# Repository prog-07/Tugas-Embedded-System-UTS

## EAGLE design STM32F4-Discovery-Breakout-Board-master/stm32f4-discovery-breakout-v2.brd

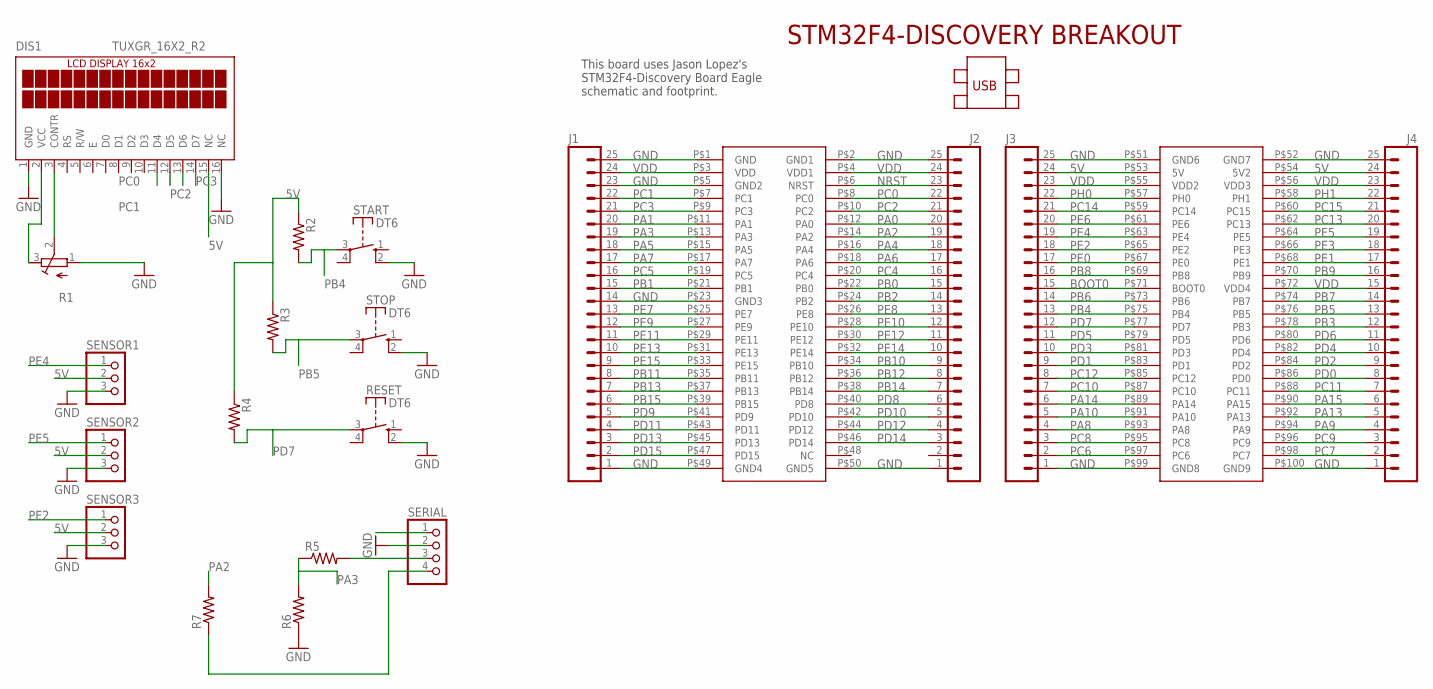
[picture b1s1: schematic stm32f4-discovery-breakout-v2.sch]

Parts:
DIS1: TUXGR_16X2_R2
J1, J2, J3, J4: M25LOCK_LONGPADS; 1X25_LOCK_LONGPADS
R1: R-TRIMM3339P; RTRIM3339P
R2, R3, R4, R5, R6, R7: R-US_0207/10; 0207/10
RESET: DT6
SENSOR1, SENSOR2, SENSOR3: PINHD-1X3; 1X03
SERIAL: PINHD-1X4; 1X04
START: DT6
STOP: DT6
U$1: STM32F4-DISCOVERY

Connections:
BOOT0: J3.15, U$1.P$71 (BOOT0)
unnamed: DIS1.2 (VCC), R1.3 (A)
unnamed: DIS1.3 (CONTR), R1.2 (S)
unnamed: R5.2, SERIAL.3
unnamed: R7.1, SERIAL.4
NRST: J2.23, U$1.P$6 (NRST)
PA0: J2.20, U$1.P$12 (PA0)
PA1: J1.20, U$1.P$11 (PA1)
PA2: J2.19, R7.2, U$1.P$14 (PA2)
PA3: J1.19, R5.1, R6.2, U$1.P$13 (PA3)
PA4: J2.18, U$1.P$16 (PA4)
PA5: J1.18, U$1.P$15 (PA5)
PA6: J2.17, U$1.P$18 (PA6)
PA7: J1.17, U$1.P$17 (PA7)
PA8: J3.4, U$1.P$93 (PA8)
PA9: J4.4, U$1.P$94 (PA9)
PA10: J3.5, U$1.P$91 (PA10)
PA13: J4.5, U$1.P$92 (PA13)
PA14: J3.6, U$1.P$89 (PA14)
PA15: J4.6, U$1.P$90 (PA15)
PB0: J2.15, U$1.P$22 (PB0)
PB1: J1.15, U$1.P$21 (PB1)
PB2: J2.14, U$1.P$24 (PB2)
PB3: J4.12, U$1.P$78 (PB3)
PB4: J3.13, R2.2, START.3, U$1.P$75 (PB4)
PB5: J4.13, R3.2, STOP.3, U$1.P$76 (PB5)
PB6: J3.14, U$1.P$73 (PB6)
PB7: J4.14, U$1.P$74 (PB7)
PB8: J3.16, U$1.P$69 (PB8)
PB9: J4.16, U$1.P$70 (PB9)
PB10: J2.9, U$1.P$34 (PB10)
PB11: J1.8, U$1.P$35 (PB11)
PB12: J2.8, U$1.P$36 (PB12)
PB13: J1.7, U$1.P$37 (PB13)
PB14: J2.7, U$1.P$38 (PB14)
PB15: J1.6, U$1.P$39 (PB15)
PC0: DIS1.11 (D4), J2.22, U$1.P$8 (PC0)
PC1: DIS1.12 (D5), J1.22, U$1.P$7 (PC1)
PC2: DIS1.13 (D6), J2.21, U$1.P$10 (PC2)
PC3: DIS1.14 (D7), J1.21, U$1.P$9 (PC3)
PC4: J2.16, U$1.P$20 (PC4)
PC5: J1.16, U$1.P$19 (PC5)
PC6: J3.2, U$1.P$97 (PC6)
PC7: J4.2, U$1.P$98 (PC7)
PC8: J3.3, U$1.P$95 (PC8)
PC9: J4.3, U$1.P$96 (PC9)
PC10: J3.7, U$1.P$87 (PC10)
PC11: J4.7, U$1.P$88 (PC11)
PC12: J3.8, U$1.P$85 (PC12)
PC13: J4.20, U$1.P$62 (PC13)
PC14: J3.21, U$1.P$59 (PC14)
PC15: J4.21, U$1.P$60 (PC15)
PD0: J4.8, U$1.P$86 (PD0)
PD1: J3.9, U$1.P$83 (PD1)
PD2: J4.9, U$1.P$84 (PD2)
PD3: J3.10, U$1.P$81 (PD3)
PD4: J4.10, U$1.P$82 (PD4)
PD5: J3.11, U$1.P$79 (PD5)
PD6: J4.11, U$1.P$80 (PD6)
PD7: J3.12, R4.2, RESET.3, U$1.P$77 (PD7)
PD8: J2.6, U$1.P$40 (PD8)
PD9: J1.5, U$1.P$41 (PD9)
PD10: J2.5, U$1.P$42 (PD10)
PD11: J1.4, U$1.P$43 (PD11)
PD12: J2.4, U$1.P$44 (PD12)
PD13: J1.3, U$1.P$45 (PD13)
PD14: J2.3, U$1.P$46 (PD14)
PD15: J1.2, U$1.P$47 (PD15)
PE0: J3.17, U$1.P$67 (PE0)
PE1: J4.17, U$1.P$68 (PE1)
PE2: J3.18, SENSOR3.1, U$1.P$65 (PE2)
PE3: J4.18, U$1.P$66 (PE3)
PE4: J3.19, SENSOR1.1, U$1.P$63 (PE4)
PE5: J4.19, SENSOR2.1, U$1.P$64 (PE5)
PE6: J3.20, U$1.P$61 (PE6)
PE7: J1.13, U$1.P$25 (PE7)
PE8: J2.13, U$1.P$26 (PE8)
PE9: J1.12, U$1.P$27 (PE9)
PE10: J2.12, U$1.P$28 (PE10)
PE11: J1.11, U$1.P$29 (PE11)
PE12: J2.11, U$1.P$30 (PE12)
PE13: J1.10, U$1.P$31 (PE13)
PE14: J2.10, U$1.P$32 (PE14)
PE15: J1.9, U$1.P$33 (PE15)
PH0: J3.22, U$1.P$57 (PH0)
PH1: J4.22, U$1.P$58 (PH1)
VDD: J1.24, J2.24, J3.23, J4.15, J4.23, U$1.P$3 (VDD), U$1.P$4 (VDD1), U$1.P$55 (VDD2), U$1.P$56 (VDD3), U$1.P$72 (VDD4)

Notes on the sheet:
This board uses Jason Lopez's STM32F4-Discovery Board Eagle schematic and footprint.

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
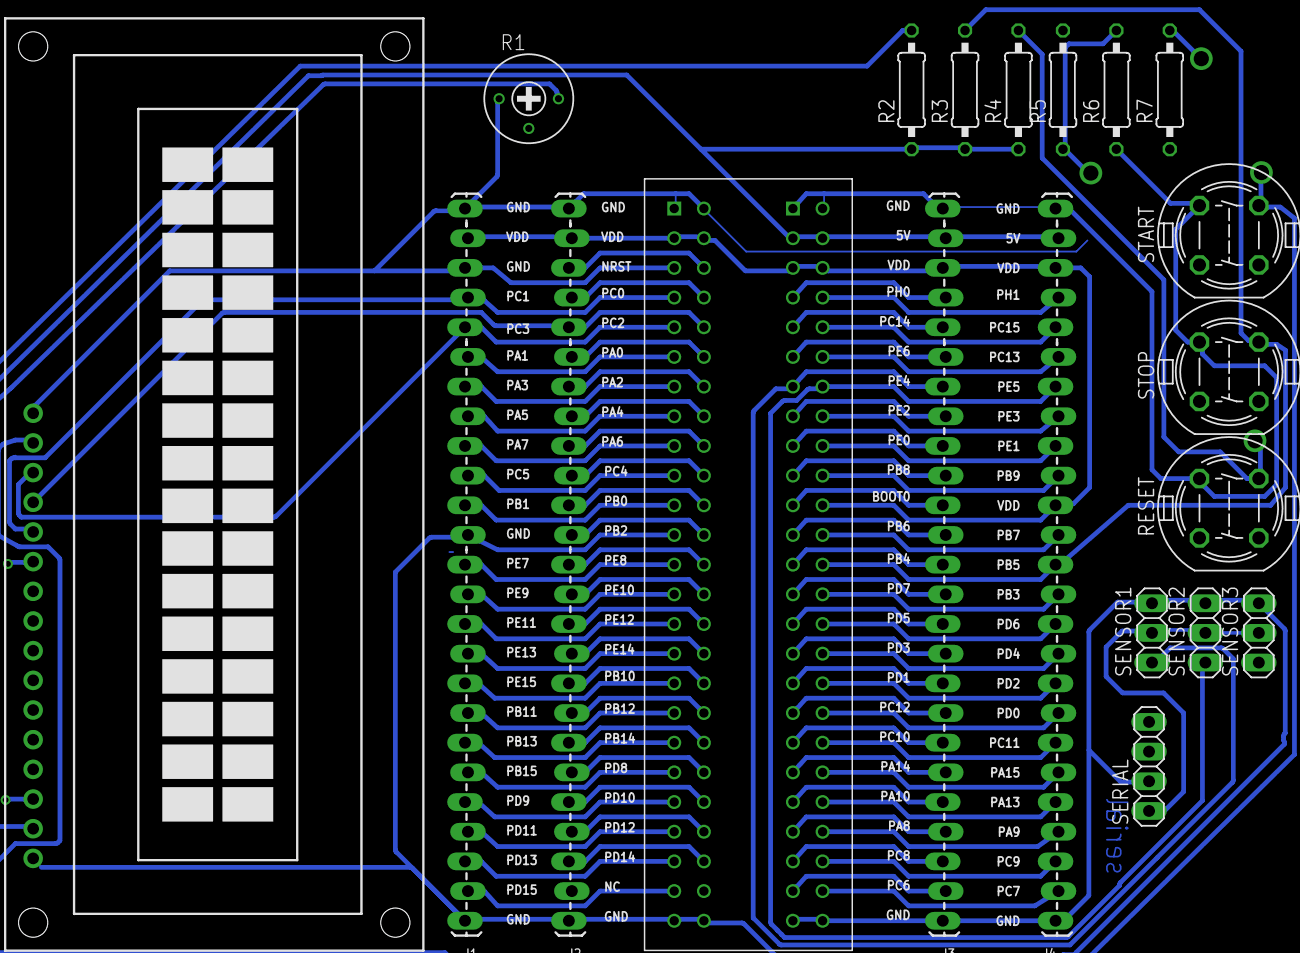
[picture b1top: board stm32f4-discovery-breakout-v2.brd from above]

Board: 2 copper layers, 20 parts (0 on the bottom side), 89 nets.

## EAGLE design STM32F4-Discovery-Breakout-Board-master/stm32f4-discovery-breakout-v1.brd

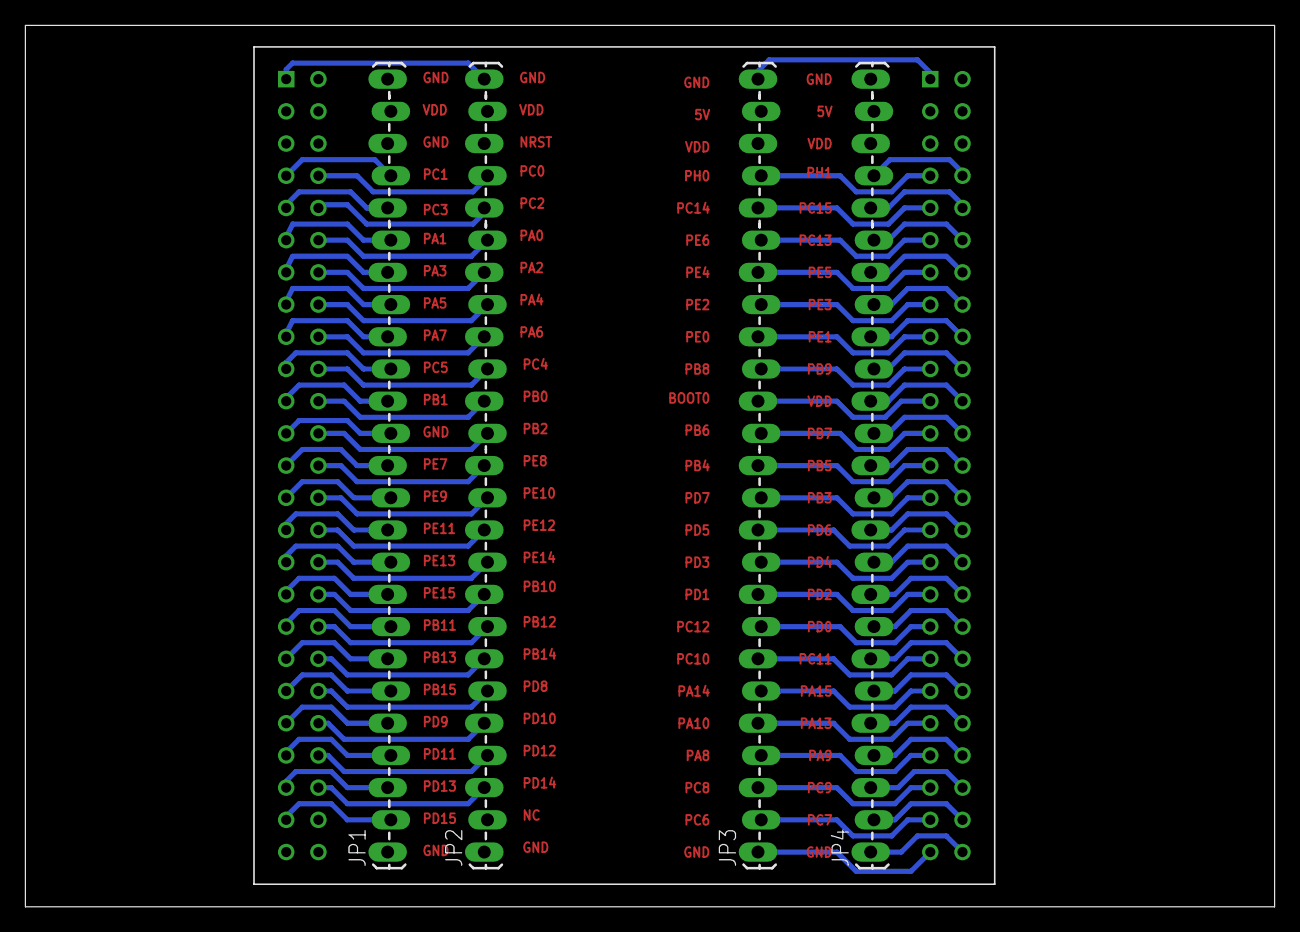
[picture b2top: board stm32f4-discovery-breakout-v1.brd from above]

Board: 2 copper layers, 98.5 x 69.5 mm, 5 parts (0 on the bottom side), 85 nets.

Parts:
JP1, JP2, JP3, JP4: M25LOCK_LONGPADS; 1X25_LOCK_LONGPADS
U$1: STM32F4-DISCOVERY

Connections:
5V: JP3.24, JP4.24, U$1.P$53, U$1.P$54
BOOT0: JP3.15, U$1.P$71
GND: JP1.1, JP1.14, JP1.23, JP1.25, JP2.1, JP2.25, JP3.1, JP3.25, JP4.1, JP4.25, U$1.P$1, U$1.P$2, U$1.P$5, U$1.P$23, U$1.P$49, U$1.P$50, U$1.P$51, U$1.P$52, U$1.P$99, U$1.P$100
NRST: JP2.23, U$1.P$6
PA0: JP2.20, U$1.P$12
PA1: JP1.20, U$1.P$11
PA2: JP2.19, U$1.P$14
PA3: JP1.19, U$1.P$13
PA4: JP2.18, U$1.P$16
PA5: JP1.18, U$1.P$15
PA6: JP2.17, U$1.P$18
PA7: JP1.17, U$1.P$17
PA8: JP3.4, U$1.P$93
PA9: JP4.4, U$1.P$94
PA10: JP3.5, U$1.P$91
PA13: JP4.5, U$1.P$92
PA14: JP3.6, U$1.P$89
PA15: JP4.6, U$1.P$90
PB0: JP2.15, U$1.P$22
PB1: JP1.15, U$1.P$21
PB2: JP2.14, U$1.P$24
PB3: JP4.12, U$1.P$78
PB4: JP3.13, U$1.P$75
PB5: JP4.13, U$1.P$76
PB6: JP3.14, U$1.P$73
PB7: JP4.14, U$1.P$74
PB8: JP3.16, U$1.P$69
PB9: JP4.16, U$1.P$70
PB10: JP2.9, U$1.P$34
PB11: JP1.8, U$1.P$35
PB12: JP2.8, U$1.P$36
PB13: JP1.7, U$1.P$37
PB14: JP2.7, U$1.P$38
PB15: JP1.6, U$1.P$39
PC0: JP2.22, U$1.P$8
PC1: JP1.22, U$1.P$7
PC2: JP2.21, U$1.P$10
PC3: JP1.21, U$1.P$9
PC4: JP2.16, U$1.P$20
PC5: JP1.16, U$1.P$19
PC6: JP3.2, U$1.P$97
PC7: JP4.2, U$1.P$98
PC8: JP3.3, U$1.P$95
PC9: JP4.3, U$1.P$96
PC10: JP3.7, U$1.P$87
PC11: JP4.7, U$1.P$88
PC12: JP3.8, U$1.P$85
PC13: JP4.20, U$1.P$62
PC14: JP3.21, U$1.P$59
PC15: JP4.21, U$1.P$60
PD0: JP4.8, U$1.P$86
PD1: JP3.9, U$1.P$83
PD2: JP4.9, U$1.P$84
PD3: JP3.10, U$1.P$81
PD4: JP4.10, U$1.P$82
PD5: JP3.11, U$1.P$79
PD6: JP4.11, U$1.P$80
PD7: JP3.12, U$1.P$77
PD8: JP2.6, U$1.P$40
PD9: JP1.5, U$1.P$41
PD10: JP2.5, U$1.P$42
PD11: JP1.4, U$1.P$43
PD12: JP2.4, U$1.P$44
PD13: JP1.3, U$1.P$45
PD14: JP2.3, U$1.P$46
PD15: JP1.2, U$1.P$47
PE0: JP3.17, U$1.P$67
PE1: JP4.17, U$1.P$68
PE2: JP3.18, U$1.P$65
PE3: JP4.18, U$1.P$66
PE4: JP3.19, U$1.P$63
PE5: JP4.19, U$1.P$64
PE6: JP3.20, U$1.P$61
PE7: JP1.13, U$1.P$25
PE8: JP2.13, U$1.P$26
PE9: JP1.12, U$1.P$27
PE10: JP2.12, U$1.P$28
PE11: JP1.11, U$1.P$29
PE12: JP2.11, U$1.P$30
PE13: JP1.10, U$1.P$31
PE14: JP2.10, U$1.P$32
PE15: JP1.9, U$1.P$33
PH0: JP3.22, U$1.P$57
PH1: JP4.22, U$1.P$58
VDD: JP1.24, JP2.24, JP3.23, JP4.15, JP4.23, U$1.P$3, U$1.P$4, U$1.P$55, U$1.P$56, U$1.P$72

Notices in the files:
parts and their libraries:
SparkFun-Connectors: Licensing: Creative Commons ShareAlike 4.0 International - https://creativecommons.org/licenses/by-sa/4.0
